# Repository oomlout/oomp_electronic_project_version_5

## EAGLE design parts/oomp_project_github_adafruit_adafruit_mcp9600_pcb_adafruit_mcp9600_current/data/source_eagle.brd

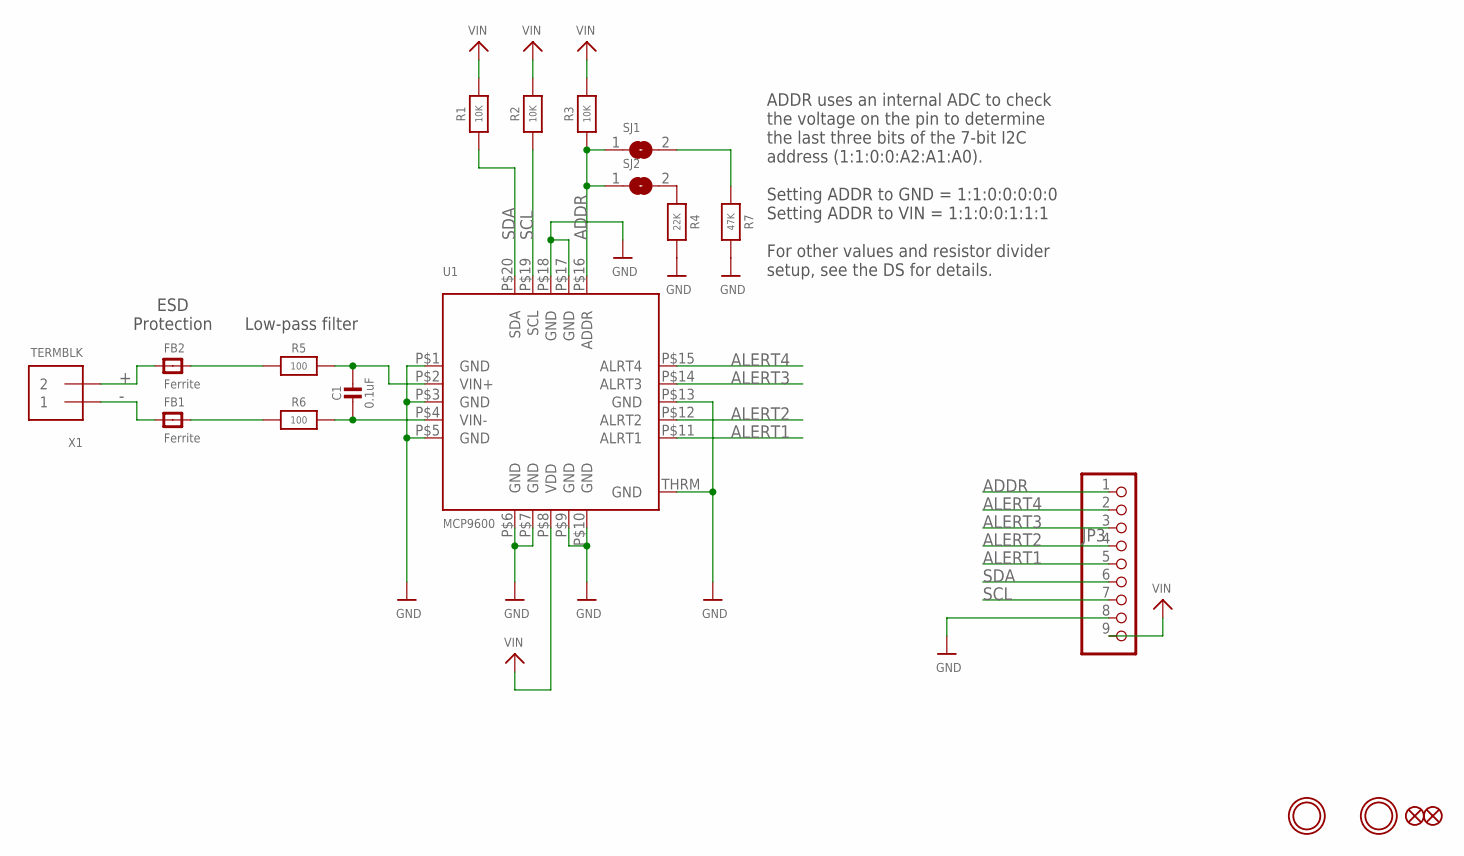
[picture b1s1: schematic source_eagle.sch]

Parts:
C1: 0.1uF; 0603-NO
FB1, FB2: Ferrite; 0805-NO
FID1, FID2: FIDUCIAL_1MM
JP3: HEADER-1X970MIL; 1X09_ROUND_70
R1, R2, R3: 10K; 0603-NO
R4: 22K; 0603-NO
R5, R6: 100; 0603-NO
R7: 47K; 0603-NO
SJ1, SJ2: SOLDERJUMPER; SOLDERJUMPER_ARROW_NOPASTE
U1: MCP9600; VQFN20_5MM
U$1, U$3: MOUNTINGHOLE2.5; MOUNTINGHOLE_2.5_PLATED
X1: TERMBLK; TERMBLOCK_1X2-3.5MM

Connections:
+: FB2.1, X1.2
-: FB1.1, X1.1
ADDR: JP3.1, R3.1, SJ1.1, SJ2.1, U1.P$16 (ADDR)
ALERT1: JP3.5, U1.P$11 (ALRT1)
ALERT2: JP3.4, U1.P$12 (ALRT2)
ALERT3: JP3.3, U1.P$14 (ALRT3)
ALERT4: JP3.2, U1.P$15 (ALRT4)
GND: JP3.8, R4.2, R7.2, U1.P$1 (GND), U1.P$3 (GND), U1.P$5 (GND), U1.P$6 (GND), U1.P$7 (GND), U1.P$9 (GND), U1.P$10 (GND), U1.P$13 (GND), U1.P$17 (GND), U1.P$18 (GND), U1.THRM (GND)
unnamed: C1.1, R5.2, U1.P$2 (VIN+)
unnamed: C1.2, R6.2, U1.P$4 (VIN-)
unnamed: FB1.2, R6.1
unnamed: FB2.2, R5.1
unnamed: R7.1, SJ1.2
unnamed: R4.1, SJ2.2
SCL: JP3.7, R2.1, U1.P$19 (SCL)
SDA: JP3.6, R1.1, U1.P$20 (SDA)
VIN: JP3.9, R1.2, R2.2, R3.2, U1.P$8 (VDD)

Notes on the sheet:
ADDR uses an internal ADC to check the voltage on the pin to determine the last three bits of the 7-bit I2C address (1:1:0:0:A2:A1:A0). Setting ADDR to GND = 1:1:0:0:0:0:0 Setting ADDR to VIN = 1:1:0:0:1:1:1 For other values and resistor divider setup, see the DS for details.
Low-pass filter
ESD Protection

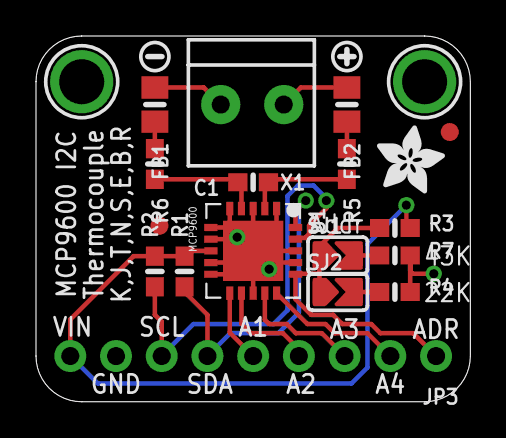
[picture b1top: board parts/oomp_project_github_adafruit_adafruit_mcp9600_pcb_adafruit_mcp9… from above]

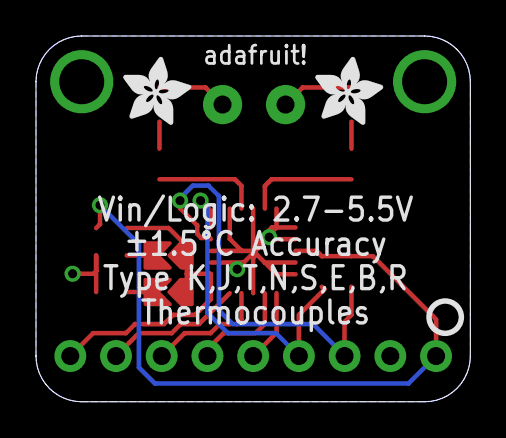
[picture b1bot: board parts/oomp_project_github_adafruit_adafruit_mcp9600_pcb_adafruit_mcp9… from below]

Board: 2 copper layers, 24.1 x 20.3 mm, 25 parts (3 on the bottom side), 17 nets.

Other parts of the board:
U$16, U$19, U$20: ADAFRUIT_3.5MM
U$17: SYMBOL_PLUS
U$18: SYMBOL_MINUS
U$21: PCBFEAT-REV-040

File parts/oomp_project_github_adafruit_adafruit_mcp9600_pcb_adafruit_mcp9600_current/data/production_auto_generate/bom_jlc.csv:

Comment,Designator,Footprint,LCSC Part #
,JP3,Adafruit MCP9600-import-fps:1X09_ROUND_70,C2932701
,"U$16,U$19,U$20",Adafruit MCP9600-import-fps:ADAFRUIT_3.5MM,
,U$21,Adafruit MCP9600-import-fps:PCBFEAT-REV-040,
,U$18,Adafruit MCP9600-import-fps:SYMBOL_MINUS,
,U$17,Adafruit MCP9600-import-fps:SYMBOL_PLUS,
0.1uF,C1,Adafruit MCP9600-import-fps:0603-NO,C14663
100,"R5,R6",Adafruit MCP9600-import-fps:0603-NO,C22775
10K,"R1,R2,R3",Adafruit MCP9600-import-fps:0603-NO,C98220
22K,R4,Adafruit MCP9600-import-fps:0603-NO,C31850
47K,R7,Adafruit MCP9600-import-fps:0603-NO,C2907042
Ferrite,"FB1,FB2",Adafruit MCP9600-import-fps:0805-NO,
MCP9600,U1,Adafruit MCP9600-import-fps:VQFN20_5MM,
TERMBLK,X1,Adafruit MCP9600-import-fps:TERMBLOCK_1X2-3.5MM,

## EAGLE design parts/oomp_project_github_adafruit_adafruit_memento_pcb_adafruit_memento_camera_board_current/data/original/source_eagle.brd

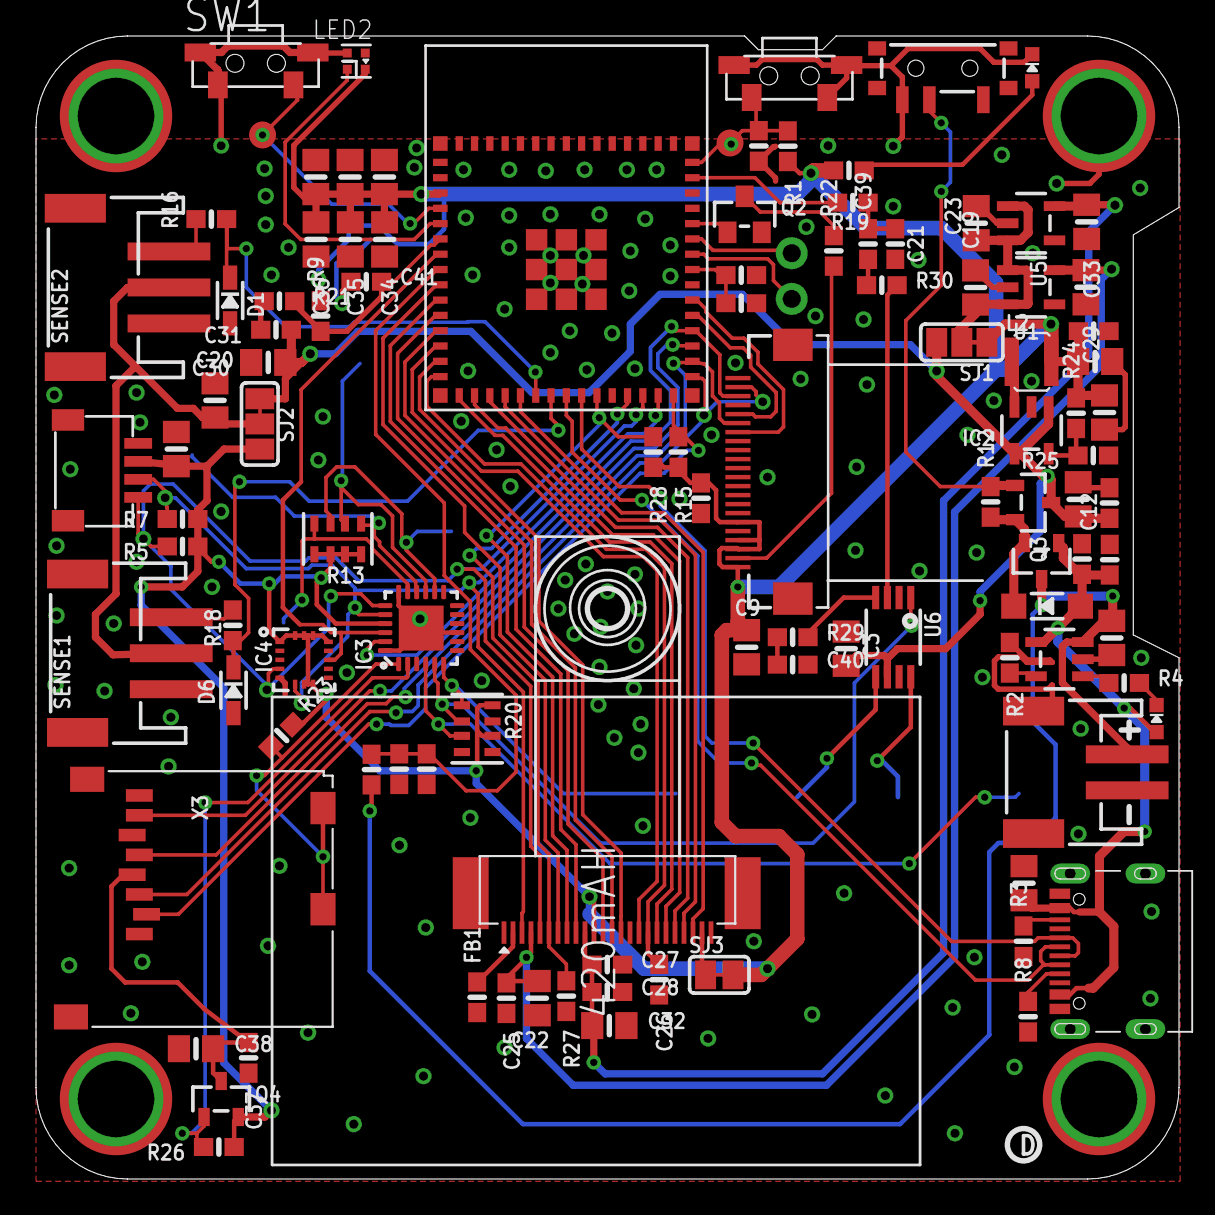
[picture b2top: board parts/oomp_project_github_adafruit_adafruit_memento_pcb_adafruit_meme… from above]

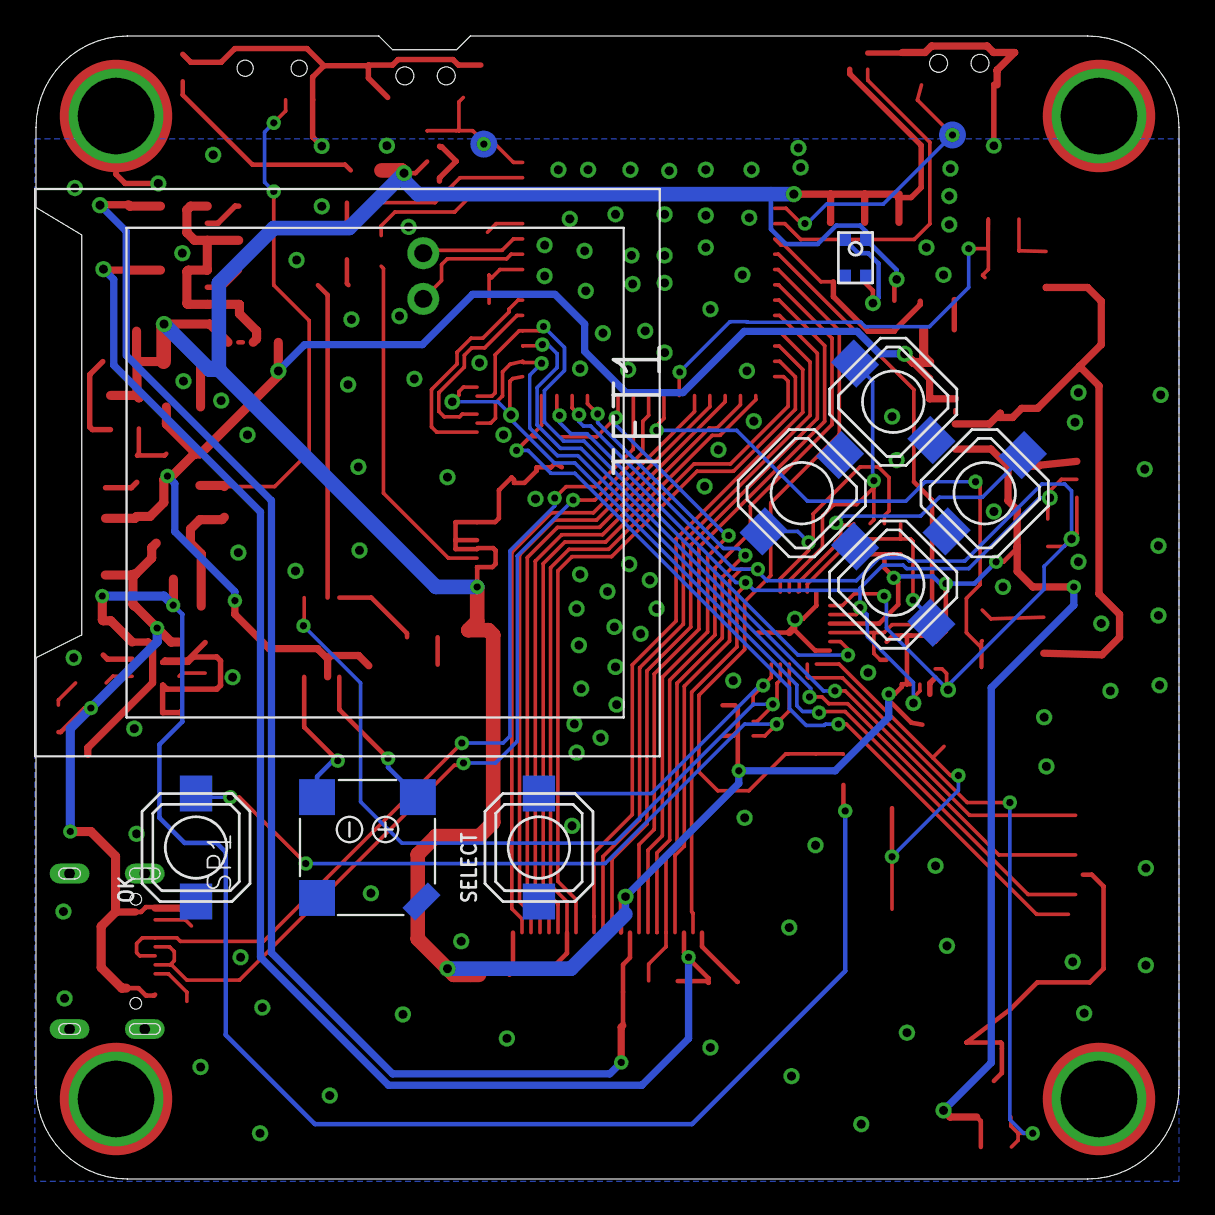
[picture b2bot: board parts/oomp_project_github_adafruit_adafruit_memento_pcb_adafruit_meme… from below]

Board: 2 copper layers, 63.5 x 63.5 mm, 125 parts (12 on the bottom side), 81 nets.

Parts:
C1, C3, C4, C7, C8, C9, C10, C11, C13, C17, C18, C19, C20, C22, C23, C29, C30, C32, C33, C34, C35, C36, C38: 10uF; 0805-NO
C2, C5, C15, C16, C25, C27, C31, C37, C39, C40, C41: 0.1uF; 0603-NO
C6, C12, C14, C28: 1uF; 0603-NO
C21: 0.01uF; 0603-NO
C26: 22pF; 0603-NO
CHG1: ORANGE; CHIPLED_0603_NOOUTLINE
CONN1: STEMMA_I2C_QT; JST_SH4
D1, D6: 3.6V; SOD-323
D4: 1N5819; SOD-123
DOWN: TL9210
FB1: ferrite; 0603-NO
IC2: TLV62569; SOT23-5
IC3: AW9523; QFN24_4MM_SMSC
IC4: LIS3DH; LGA16_3X3MM
JP2: UART; 1X02_ROUND
L2: 2.2uH/NRH2412T2R2MNGH; INDUCTOR_TAIYOYUDEN_NR3015
LED2: WS2812B_SK6805_1515; SK6805_1515
LEFT: TL9210
OK: TL9210
ON: GREEN; CHIPLED_0603_NOOUTLINE
Q1, Q3, Q4: AO3401; SOT23-R
Q2: BSS138; SOT23-WIDE
R1, R5, R7, R15, R21, R26: 10K; 0603-NO
R2, R3, R4, R8: 5.1K; 0603-NO
R6, R9, R12, R14, R23, R27, R28, R29, R30: 47K; 0603-NO
R10, R11, R17: 1Meg; 0603-NO
R13, R20: 10K Pack; RESPACK_4X0603
R16, R18, R19: 1K; 0603-NO
R22: 22; 0603-NO
R24: 450K; 0603-NO
R25: 100K; 0603-NO
RIGHT: TL9210
SELECT: TL9210
SENSE1, SENSE2: JST PH 3; JSTPH3
SJ1, SJ2: SOLDERJUMPER_2WAY_OPEN_NOPASTE
SJ3: SOLDERJUMPER_CLOSEDWIRE
SP1: 7.5mm SPK; BUZZER_SMT_7.5MM
SW1, SW2: RA_TACT; SPST_TACTILE_RA
SW4: SPDT R/A; SPDT_SMT_SSSS811101
TFT1: DISP_TFT_1.54IN_240X240_22P; TFT_1.54IN_240X240_22PIN
TP1, TP2, TP7, TP8: TESTPOINT_ROUND_1.5MM_NO
TP3, TP4, TP5, TP6: SEWTAP_SMTNUTM3; SMT_NUT_3MM
U1: TLV74328; SOT23-5
U2: MCP73831T-2ACI/OT; SOT23-5
U3: ESP32-S3-MINI-1-N4R2; ESP32-S2-MINI-1
U5: TLV74315; SOT23-5
U6: PAM8302; MSOP8_0.65MM
U7: Microphone; MEMS_MIC_2.75X1.85
U$83: LIPO_552535
U$119: MEMENTO_TOP
U$120: MEMENTO_BOT
U$121: PCBFEAT-REV-040
UP: TL9210
X1: JST PH 2; JSTPH2_BATT
X2: CAMERA_OV2640; OV2640FSL
X3: MicroSD; MICROSD
X4: USB C; USB_C_CUSB31-CFM2AX-01-X

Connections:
1.5V: C27.1, C28.1, C32.1, C33.1, U5.5, X2.10
2.8V: C22.1, C25.1, C29.1, U1.5, X2.4
3.3V: C2.1, C4.1, C5.1, C7.1, C9.2, C10.1, C13.1, C17.1, C18.1, C34.1, C35.1, C36.1, CONN1.2, IC3.21, IC4.1, IC4.7, IC4.8, IC4.13, IC4.14, IC4.15, IC4.16, L2.P$2, LED2.2, Q4.2, R1.2, R5.1, R6.2, R7.1, R9.2, R13.5, R13.6, R13.7, R13.8, R15.2, R20.6, R20.8, R23.2, R24.2, R26.1, R28.2, SJ1.1, SJ2.3, SJ3.2, TFT1.1, TFT1.3, TFT1.4, TFT1.6, U3.3, U7.1, X2.11
A1_JST1: R18.1, SENSE1.3
AD0: D1.C, R16.2, U3.21
AD1: D6.C, R18.2, U3.22
AGND: FB1.2, X2.2
BACKLIGHT: Q2.1, U3.41
BATT_MON: C16.1, R10.2, R11.1, U3.8
BOOT0/SHUTTER: SW1.1, TP1.P$1, TP8.P$1, U3.4
BUTTONOK: IC3.4, OK.2, R20.3
BUTTONSEL: IC3.6, R20.1, SELECT.2
CAM_PWDN: R28.1, U3.25, X2.8
CAM_RST: R27.1, U3.27, X2.6
CARDDET: IC3.1, R23.1, X3.CD1, X3.CD2
CARD_CS: R15.1, U3.30, X3.2
CC1: R8.2, X4.A5
CC2: R3.2, X4.B5
D10_JST: R16.1, SENSE2.3
D+: U3.24, X4.A6, X4.B6
D-: U3.23, X4.A7, X4.B7
DATA1: SJ3.1, X2.23
DATA2: U3.17, X2.19
DATA3: U3.19, X2.21
DATA4: U3.20, X2.22
DATA5: U3.18, X2.20
DATA6: U3.16, X2.18
DATA7: U3.14, X2.16
DATA8: U3.13, X2.14
DATA9: U3.11, X2.12
DOWN: DOWN.2, IC3.17, R13.4
EN: Q3.1, R12.2, SW4.B
EXT_XCLK: U3.12, X2.13
FB: IC2.5, R24.1, R25.2
GND: C1.2, C2.2, C3.2, C4.2, C5.2, C6.2, C7.2, C8.2, C9.1, C10.2, C11.2, C12.2, C13.2, C14.2, C15.2, C16.2, C17.2, C18.2, C19.2, C20.2, C21.1, C22.2, C23.2, C25.2, C26.2, C27.2, C28.2, C29.2, C30.2, C31.2, C32.2, C33.2, C34.2, C35.2, C36.2, C37.2, C38.1, C40.2, CONN1.1, CONN1.MT1, CONN1.MT2, D1.A, D6.A, DOWN.1, FB1.1, IC2.2, IC3.9, IC3.18, IC3.24, IC3.THERM, IC4.5, IC4.10, IC4.12, LED2.4, LEFT.1, OK.1, ON.C, Q2.2, R2.1, R3.1, R8.1, R11.2, R14.1, R17.1, R20.7, R21.1, R25.1, R27.2, RIGHT.1, SELECT.1, SENSE1.1, SENSE1.NC1, SENSE1.NC2, SENSE2.1, SENSE2.NC1, SENSE2.NC2, SW1.2, SW1.MT1, SW1.MT2, SW2.1, SW2.MT1, SW2.MT2, SW4.C, TFT1.5, TFT1.7, TFT1.8, TFT1.9, TFT1.10, TFT1.11, TFT1.12, TFT1.13, TFT1.14, TFT1.15, TFT1.22, TFT1.SUPPORT1, TFT1.SUPPORT2, TP3.P$1, TP4.P$1, TP5.P$1, TP6.P$1, U1.2, U2.2, U3.1, U3.2, U3.42, U3.43, U3.46, U3.47, U3.48, U3.49, U3.50, U3.51, U3.52, U3.53, U3.54, U3.55, U3.56, U3.57, U3.58, U3.59, U3.60, U3.61, U3.62, U3.63, U3.64, U3.65, U3.66, U3.67, U3.68, U3.69, U3.70, U3.71, U3.72, U3.73, U5.2, U6.7, U7.2, U7.3, UP.1, X1.1, X1.NC1, X1.NC2, X2.15, X2.SPRT1, X2.SPRT2, X3.6, X3.MT1, X3.MT2, X4.A1B12, X4.B1A12
HSYNC: U3.10, X2.9
IO42_DBLTAP: C6.1, R17.2, U3.38
IRQ: IC3.22, IC4.11, U3.7
LED_K: R22.1, TFT1.2
LEFT: IC3.16, LEFT.2, R13.1
MIC: C41.2, R9.1, R21.2, U3.6
MISO: U3.33, X3.7
MOSI: TFT1.21, U3.31, X3.3
unnamed: C41.1, U7.4
unnamed: ON.A, R6.1
unnamed: R4.1, U2.1
unnamed: Q2.3, R22.2
unnamed: CHG1.C, R4.2
unnamed: R29.2, U6.4
unnamed: R30.2, U6.3
unnamed: R2.2, U2.5
unnamed: C40.1, R29.1
unnamed: SP1.-, U6.8
unnamed: SP1.+, U6.5
unnamed: C39.1, R30.1
unnamed: C21.2, C39.2, R19.1
unnamed: IC2.3, L2.P$1
unnamed: D4.C, Q1.2, Q3.2, R12.1
NEOPIXEL: LED2.1, U3.5
PCLK: C26.1, U3.15, X2.17
PERIPH_RST: IC3.23, TFT1.20, U3.34
RESET: C14.1, R1.1, SW2.2, TP2.P$1, TP7.P$1, U3.45
RIGHT: IC3.14, R13.3, RIGHT.2
RXD0: JP2.2, U3.40
SCK: TFT1.17, U3.32, X3.5
SCL: CONN1.4, IC3.19, IC4.4, R5.2, U3.28, X2.5
SDA: CONN1.3, IC3.20, IC4.6, R7.2, U3.29, X2.3
SD_PWR: IC3.2, Q4.1, R26.2
SD_VDD: C37.1, C38.2, Q4.3, X3.4
SPKR: R19.2, U3.44
SPKR_SD: IC3.5, R20.2, U6.1
TFT_CS: TFT1.18, U3.35
TFT_DC: TFT1.16, U3.36
TXD0: JP2.1, U3.39
UP: IC3.15, R13.2, UP.2
VBAT: C8.1, Q1.3, R10.1, U2.3, X1.2
VBUS: C1.1, C15.1, CHG1.A, D4.A, Q1.1, R14.2, U2.4, X4.A4B9, X4.B4A9
VCC: C20.1, SENSE1.2, SENSE2.2, SJ2.2
VHIGH: C3.1, C11.1, C12.1, C30.1, C31.1, IC2.1, IC2.4, Q3.3, SJ1.3, SJ2.1, U6.6
VPWR: C19.1, C23.1, SJ1.2, U1.1, U1.3, U5.1, U5.3
VSYNC: U3.9, X2.7

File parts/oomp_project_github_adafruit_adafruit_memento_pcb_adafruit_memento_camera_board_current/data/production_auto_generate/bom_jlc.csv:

Comment,Designator,Footprint,LCSC Part #
,U$83,Adafruit MEMENTO Camera Board-import-fps:LIPO_552535,
,U$120,Adafruit MEMENTO Camera Board-import-fps:MEMENTO_BOT,
,U$119,Adafruit MEMENTO Camera Board-import-fps:MEMENTO_TOP,
,U$121,Adafruit MEMENTO Camera Board-import-fps:PCBFEAT-REV-040,
,"TP1,TP2,TP7,TP8",Adafruit MEMENTO Camera Board-import-fps:TESTPOINT_ROUND_1.5MM_NO,
0.01uF,C21,Adafruit MEMENTO Camera Board-import-fps:0603-NO,C5137477
0.1uF,"C2,C5,C15,C16,C25,C27,C31,C37,C39,C40,C41",Adafruit MEMENTO Camera Board-import-fps:0603-NO,C14663
100K,R25,Adafruit MEMENTO Camera Board-import-fps:0603-NO,C25803
10K,"R1,R5,R7,R15,R21,R26",Adafruit MEMENTO Camera Board-import-fps:0603-NO,C98220
10K Pack,"R13,R20",Adafruit MEMENTO Camera Board-import-fps:RESPACK_4X0603,C98220
10uF,"C1,C3,C4,C7,C8,C9,C10,C11,C13,C17,C18,C19,C20,C22,C23,C29,C30,C32,C33,C34,C35,C36,C38",Adafruit MEMENTO Camera Board-import-fps:0805-NO,
1K,"R16,R18,R19",Adafruit MEMENTO Camera Board-import-fps:0603-NO,C2907002
1Meg,"R10,R11,R17",Adafruit MEMENTO Camera Board-import-fps:0603-NO,C2907003
1N5819,D4,Adafruit MEMENTO Camera Board-import-fps:SOD-123,
1uF,"C6,C12,C14,C28",Adafruit MEMENTO Camera Board-import-fps:0603-NO,C5673
2.2uH/NRH2412T2R2MNGH,L2,Adafruit MEMENTO Camera Board-import-fps:INDUCTOR_TAIYOYUDEN_NR3015,
22,R22,Adafruit MEMENTO Camera Board-import-fps:0603-NO,C23345
22pF,C26,Adafruit MEMENTO Camera Board-import-fps:0603-NO,C105620
3.6V,"D1,D6",Adafruit MEMENTO Camera Board-import-fps:SOD-323,
450K,R24,Adafruit MEMENTO Camera Board-import-fps:0603-NO,
47K,"R6,R9,R12,R14,R23,R27,R28,R29,R30",Adafruit MEMENTO Camera Board-import-fps:0603-NO,C2907042
5.1K,"R2,R3,R4,R8",Adafruit MEMENTO Camera Board-import-fps:0603-NO,C23186
7.5mm SPK,SP1,Adafruit MEMENTO Camera Board-import-fps:BUZZER_SMT_7.5MM,
AO3401,"Q1,Q3,Q4",Adafruit MEMENTO Camera Board-import-fps:SOT23-R,
AW9523,IC3,Adafruit MEMENTO Camera Board-import-fps:QFN24_4MM_SMSC,
BSS138,Q2,Adafruit MEMENTO Camera Board-import-fps:SOT23-WIDE,C52895
CAMERA_OV2640,X2,Adafruit MEMENTO Camera Board-import-fps:OV2640FSL,
DISP_TFT_1.54IN_240X240_22P,TFT1,Adafruit MEMENTO Camera Board-import-fps:TFT_1.54IN_240X240_22PIN,
ESP32-S3-MINI-1-N4R2,U3,Adafruit MEMENTO Camera Board-import-fps:ESP32-S2-MINI-1,
ferrite,FB1,Adafruit MEMENTO Camera Board-import-fps:0603-NO,
GREEN,ON0,Adafruit MEMENTO Camera Board-import-fps:CHIPLED_0603_NOOUTLINE,
JST PH 2,X1,Adafruit MEMENTO Camera Board-import-fps:JSTPH2_BATT,
JST PH 3,"SENSE1,SENSE2",Adafruit MEMENTO Camera Board-import-fps:JSTPH3,
LIS3DH,IC4,Adafruit MEMENTO Camera Board-import-fps:LGA16_3X3MM,
MCP73831T-2ACI/OT,U2,Adafruit MEMENTO Camera Board-import-fps:SOT23-5,
Microphone,U7,Adafruit MEMENTO Camera Board-import-fps:MEMS_MIC_2.75X1.85,
MicroSD,X3,Adafruit MEMENTO Camera Board-import-fps:MICROSD,
ORANGE,CHG1,Adafruit MEMENTO Camera Board-import-fps:CHIPLED_0603_NOOUTLINE,
PAM8302,U6,Adafruit MEMENTO Camera Board-import-fps:MSOP8_0.65MM,
RA_TACT,"SW1,SW2",Adafruit MEMENTO Camera Board-import-fps:SPST_TACTILE_RA,
SPDT R/A,SW4,Adafruit MEMENTO Camera Board-import-fps:SPDT_SMT_SSSS811101,
STEMMA_I2C_QT,CONN1,Adafruit MEMENTO Camera Board-import-fps:JST_SH4,C160404
TL9210,"DOWN0,LEFT0,OK0,RIGHT0,SELECT0,UP0",Adafruit MEMENTO Camera Board-import-fps:TL9210,
TLV62569,IC2,Adafruit MEMENTO Camera Board-import-fps:SOT23-5,
TLV74315,U5,Adafruit MEMENTO Camera Board-import-fps:SOT23-5,
TLV74328,U1,Adafruit MEMENTO Camera Board-import-fps:SOT23-5,
UART,JP2,Adafruit MEMENTO Camera Board-import-fps:1X02_ROUND,C492401
USB C,X4,Adafruit MEMENTO Camera Board-import-fps:USB_C_CUSB31-CFM2AX-01-X,
WS2812B_SK6805_1515,LED2,Adafruit MEMENTO Camera Board-import-fps:SK6805_1515,

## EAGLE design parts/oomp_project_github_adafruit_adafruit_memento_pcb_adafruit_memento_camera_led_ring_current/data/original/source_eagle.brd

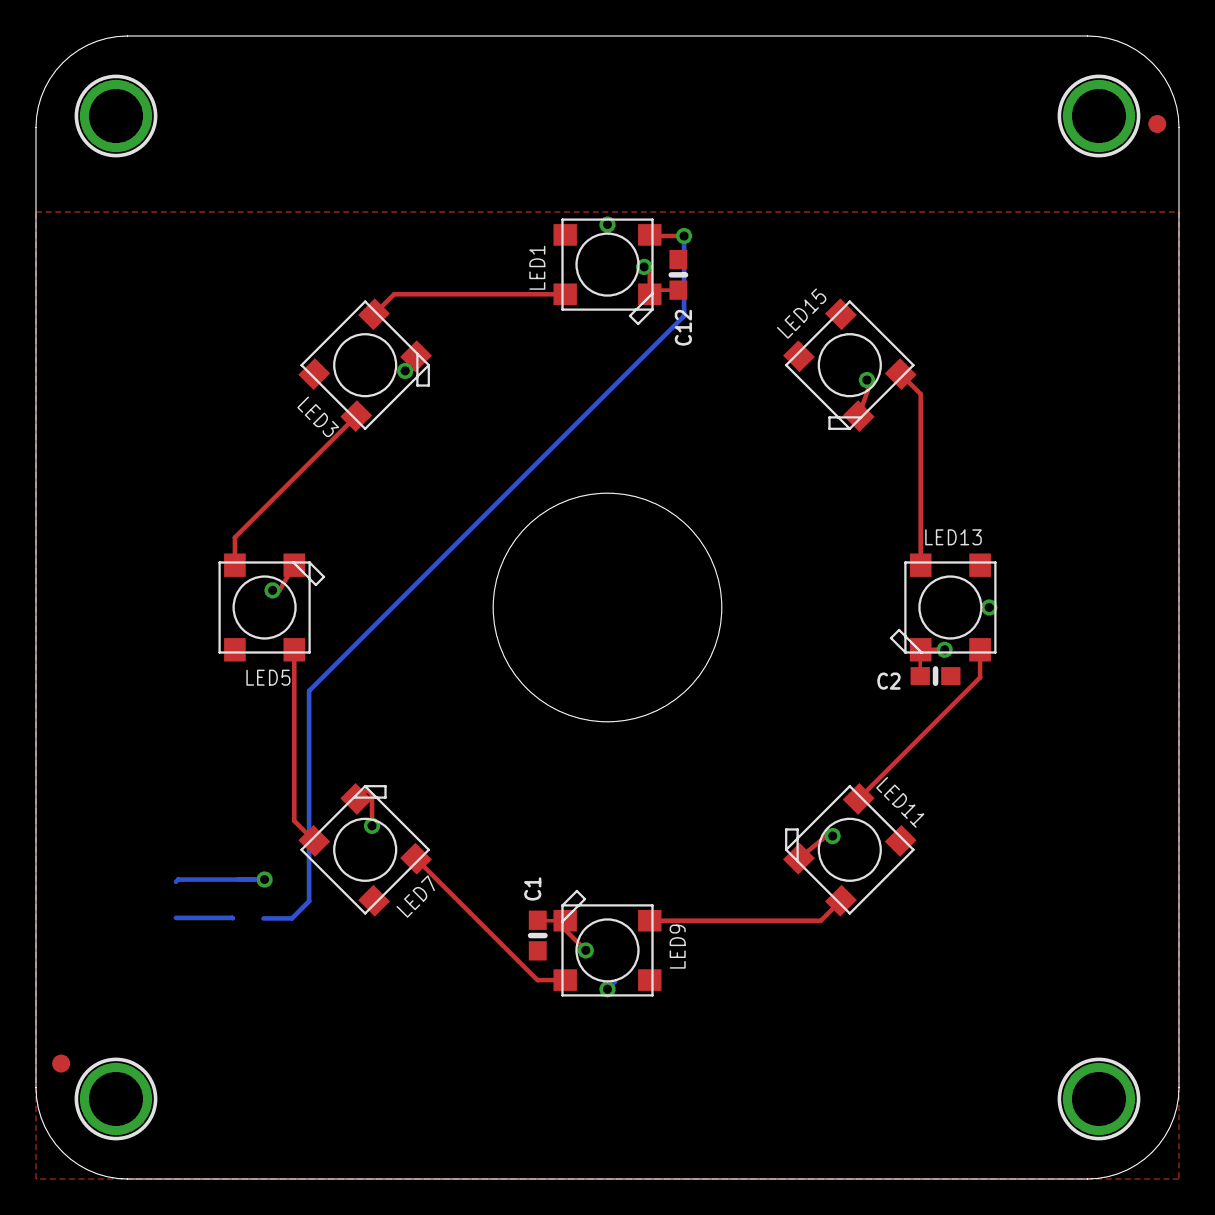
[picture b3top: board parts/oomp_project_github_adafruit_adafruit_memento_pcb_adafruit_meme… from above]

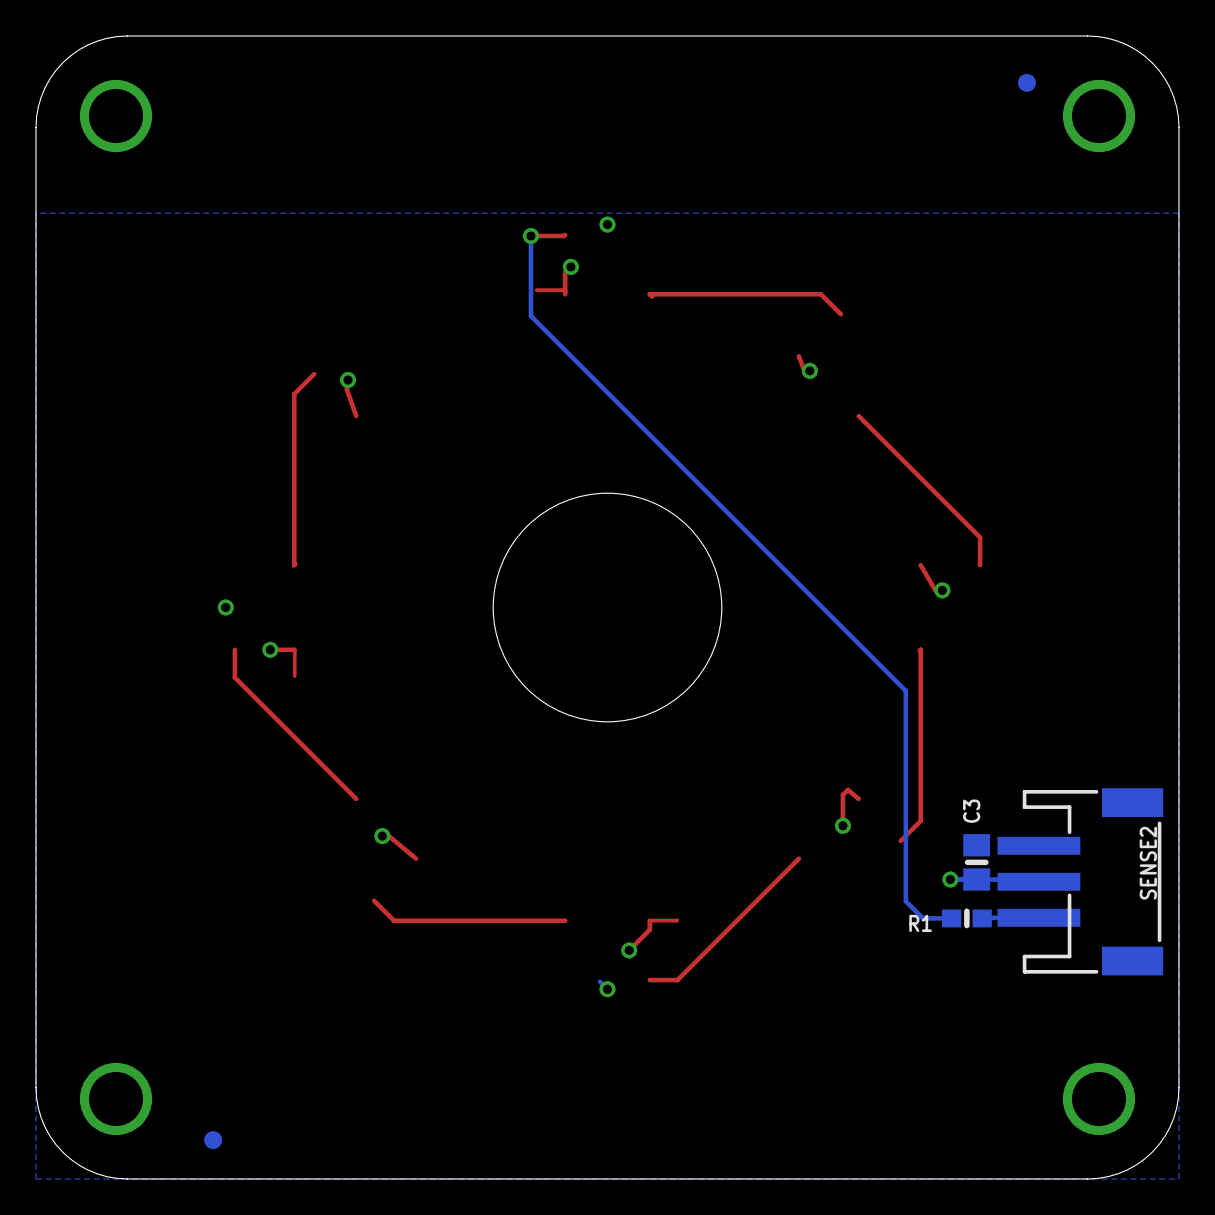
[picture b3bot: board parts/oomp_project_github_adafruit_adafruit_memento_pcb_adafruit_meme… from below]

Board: 2 copper layers, 63.5 x 63.5 mm, 24 parts (6 on the bottom side), 11 nets.

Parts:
C1, C2, C12: 1uF; 0603-NO
C3: 10uF; 0805-NO
FID1, FID2, FID3, FID4: FIDUCIAL_1MM
LED1, LED3, LED5, LED7, LED9, LED11, LED13, LED15: WS2812B_5050N; WS2812B-NARROW
R1: 470; 0603-NO
SENSE2: JST PH 3; JSTPH3
U$1, U$2, U$3, U$4: MOUNTINGHOLE3.0THIN; MOUNTINGHOLE_3.0_PLATEDTHIN
U$8: MEMENTO_LED_BOT
U$9: MEMENTO_LED_TOP

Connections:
+5V: C1.1, C2.1, C3.1, C12.1, LED1.1-VDD, LED3.1-VDD, LED5.1-VDD, LED7.1-VDD, LED9.1-VDD, LED11.1-VDD, LED13.1-VDD, LED15.1-VDD, SENSE2.2
GND: C1.2, C2.2, C3.2, C12.2, LED1.3-GND, LED3.3-GND, LED5.3-GND, LED7.3-GND, LED9.3-GND, LED11.3-GND, LED13.3-GND, LED15.3-GND, SENSE2.1, SENSE2.NC1, SENSE2.NC2
IN: R1.1, SENSE2.3
unnamed: LED1.2-DOUT, LED3.4-DIN
unnamed: LED3.2-DOUT, LED5.4-DIN
unnamed: LED5.2-DOUT, LED7.4-DIN
unnamed: LED9.2-DOUT, LED11.4-DIN
unnamed: LED11.2-DOUT, LED13.4-DIN
unnamed: LED13.2-DOUT, LED15.4-DIN
unnamed: LED7.2-DOUT, LED9.4-DIN
unnamed: LED1.4-DIN, R1.2

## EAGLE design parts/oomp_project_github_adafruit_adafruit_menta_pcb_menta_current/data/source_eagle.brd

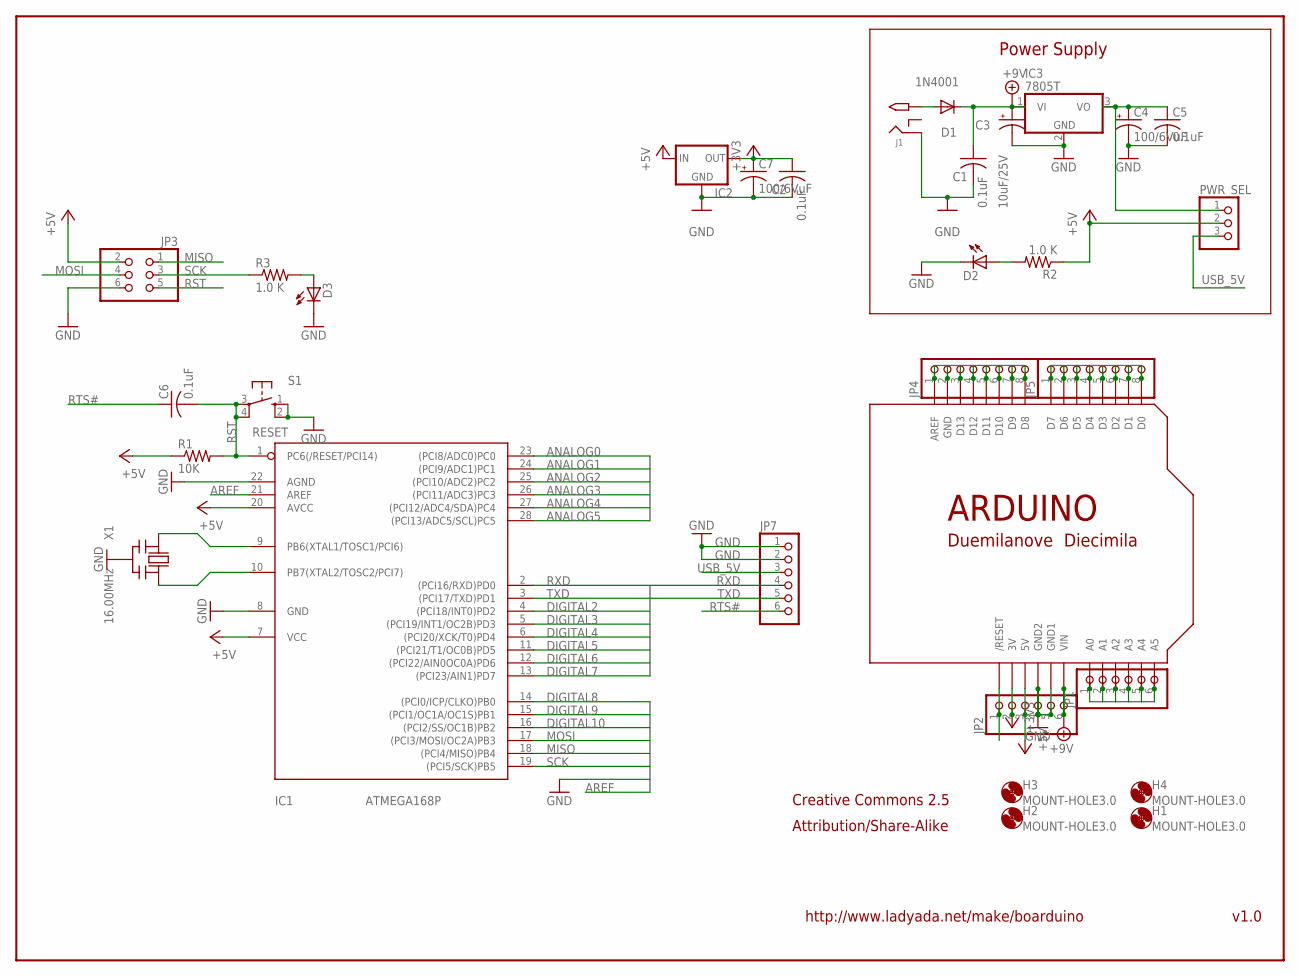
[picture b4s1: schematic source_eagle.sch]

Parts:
C1, C2, C5, C6: 0.1uF; C025-025X050
C3: 10uF/25V; E2,5-6
C4, C7: 100/6VuF; E2,5-6
D1: 1N4001; DO41-10
D2: LED3MM
D3: Green; LED3MM
H1, H2, H3, H4: MOUNT-HOLE3.0; 3,0
IC1: ATMEGA168P; DIL28/3
IC2: MCP1700INLINE; TO92-INLINE
IC3: 7805T; TO220H
J1: 2.1MMJACK; PJ-102A
JP1, JP2: PINHD-1X6CB; 1X06-CLEANBIG
JP3: PINHD-2X3; 2X03
JP4, JP5: PINHD-1X8CLEANBIG; 1X08-CLEANBIG
JP7: PINHD-1X6CLEAN; 1X06-CLEAN
PWR_SEL: PINHD-1X3; 1X03
R1: 10K; 0207/10
R2, R3: 1.0 K; 0207/10
S1: RESET; B3F-10XX
U$2: ARDUINO-NOHOLE
X1: 16.00MHz; CERM_OSC

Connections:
+3V3: C2.1, C7.+, IC2.3 (OUT), JP2.2, U$2.3V
+5V: IC1.7 (VCC), IC1.20 (AVCC), IC2.2 (IN), JP2.3, JP3.2, PWR_SEL.2, R1.1, R2.1, U$2.5V
+9V: C1.1, C3.+, D1.C, IC3.1 (VI), JP2.6, U$2.VIN
ANALOG0: IC1.23 ((PCI8/ADC0)PC0), JP1.1, U$2.A0
ANALOG1: IC1.24 ((PCI9/ADC1)PC1), JP1.2, U$2.A1
ANALOG2: IC1.25 ((PCI10/ADC2)PC2), JP1.3, U$2.A2
ANALOG3: IC1.26 ((PCI11/ADC3)PC3), JP1.4, U$2.A3
ANALOG4: IC1.27 ((PCI12/ADC4/SDA)PC4), JP1.5, U$2.A4
ANALOG5: IC1.28 ((PCI13/ADC5/SCL)PC5), JP1.6, U$2.A5
AREF: IC1.21 (AREF), JP4.1, U$2.AREF
DIGITAL2: IC1.4 ((PCI18/INT0)PD2), JP5.6, U$2.D2
DIGITAL3: IC1.5 ((PCI19/INT1/OC2B)PD3), JP5.5, U$2.D3
DIGITAL4: IC1.6 ((PCI20/XCK/T0)PD4), JP5.4, U$2.D4
DIGITAL5: IC1.11 ((PCI21/T1/OC0B)PD5), JP5.3, U$2.D5
DIGITAL6: IC1.12 ((PCI22/AIN0OC0A)PD6), JP5.2, U$2.D6
DIGITAL7: IC1.13 ((PCI23/AIN1)PD7), JP5.1, U$2.D7
DIGITAL8: IC1.14 ((PCI0/ICP/CLKO)PB0), JP4.8, U$2.D8
DIGITAL9: IC1.15 ((PCI1/OC1A/OC1S)PB1), JP4.7, U$2.D9
DIGITAL10: IC1.16 ((PCI2/SS/OC1B)PB2), JP4.6, U$2.D10
GND: C1.2, C2.2, C3.-, C4.-, C5.2, C7.-, D2.K (C), D3.K (C), IC1.8 (GND), IC1.22 (AGND), IC2.1 (GND), IC3.2 (GND), J1.RING, JP2.4, JP2.5, JP3.6, JP4.2, JP7.1, JP7.2, S1.1 (S), S1.2 (S1), U$2.GND, U$2.GND1, U$2.GND2, X1.P$2 (GND)
MISO: IC1.18 ((PCI4/MISO)PB4), JP3.1, JP4.4, U$2.D12
MOSI: IC1.17 ((PCI3/MOSI/OC2A)PB3), JP3.4, JP4.5, U$2.D11
unnamed: IC1.9 (PB6(XTAL1/TOSC1/PCI6)), X1.P$1 (IN)
unnamed: IC1.10 (PB7(XTAL2/TOSC2/PCI7)), X1.P$3 (OUT)
unnamed: D2.A, R2.2
unnamed: D3.A, R3.2
unnamed: C4.+, C5.1, IC3.3 (VO), PWR_SEL.1
unnamed: D1.A, J1.TIP
RST: C6.2, IC1.1 (PC6(/RESET/PCI14)), JP2.1, JP3.5, R1.2, S1.3, S1.4 (P1), U$2.RESET (/RESET)
RTS#: C6.1, JP7.6
RXD: IC1.2 ((PCI16/RXD)PD0), JP5.8, JP7.4, U$2.D0
SCK: IC1.19 ((PCI5/SCK)PB5), JP3.3, JP4.3, R3.1, U$2.D13
TXD: IC1.3 ((PCI17/TXD)PD1), JP5.7, JP7.5, U$2.D1
USB_5V: JP7.3, PWR_SEL.3

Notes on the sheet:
Power Supply
v1.0
http://www.ladyada.net/make/boarduino
Creative Commons 2.5
Attribution/Share-Alike

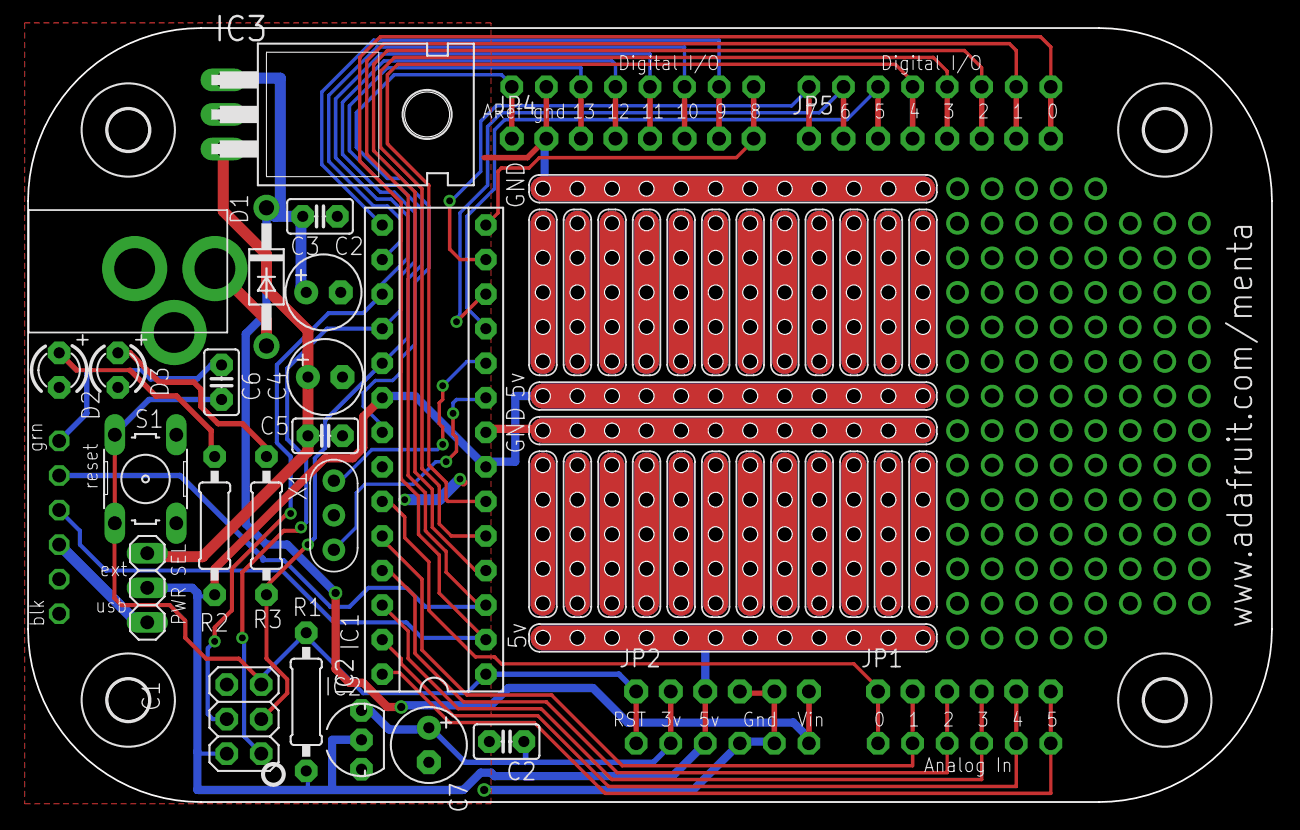
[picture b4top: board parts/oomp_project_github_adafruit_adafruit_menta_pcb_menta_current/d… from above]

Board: 2 copper layers, 91.4 x 56.9 mm, 60 parts (1 on the bottom side), 34 nets.

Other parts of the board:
U$3, U$4, U$5, U$6: 12-STRIP
U$7, U$8, U$9, U$10, U$11, U$12, U$13, U$14, U$15, U$16, U$17, U$18, U$19, U$20, U$21, U$22, U$23, U$24, U$25, U$26, U$27, U$28, U$29, U$30: 5-STRIP
U$31: ALTOIDSTIN-DIM

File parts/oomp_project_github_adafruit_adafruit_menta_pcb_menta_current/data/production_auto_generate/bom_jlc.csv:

Comment,Designator,Footprint,LCSC Part #
,PWR_SEL0,menta-import-fps:1X03,C49257
,JP7,menta-import-fps:1X06-CLEAN,C37208
,"JP1,JP2",menta-import-fps:1X06-CLEANBIG,C37208
,"JP4,JP5",menta-import-fps:1X08-CLEANBIG,C492421
,JP3,menta-import-fps:2X03,
,U$31,menta-import-fps:ALTOIDSTIN-DIM,
,D2,menta-import-fps:LED3MM,
,IC2,menta-import-fps:TO92-INLINE,
0.1uF,"C1,C2,C5,C6",menta-import-fps:C025-025X050,
1.0 K,"R2,R3",menta-import-fps:0207_10,
100/6VuF,"C4,C7","menta-import-fps:E2,5-6",
10K,R1,menta-import-fps:0207_10,
10uF/25V,C3,"menta-import-fps:E2,5-6",
1N4001,D1,menta-import-fps:DO41-10,
2.1MMJACK,J1,menta-import-fps:PJ-102A,
7805T,IC3,menta-import-fps:TO220H,
ARDUINO-NOHOLE,U$2,menta-import-fps:ARDUINO-NOHOLE,
ATMEGA168P,IC1,menta-import-fps:DIL28_3,
Green,D3,menta-import-fps:LED3MM,
RESET,S1,menta-import-fps:B3F-10XX,

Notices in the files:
parts and their libraries:
microbuilder: This work is placed in the public domain, and may be freely used for commercial and non-commercial work with the following conditions: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
COPYRIGHT: Copyright (C) 2018 Accelerated Designs. All rights reserved
